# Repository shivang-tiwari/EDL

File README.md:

# EDL
This repository has all the work done in EDL, 2022

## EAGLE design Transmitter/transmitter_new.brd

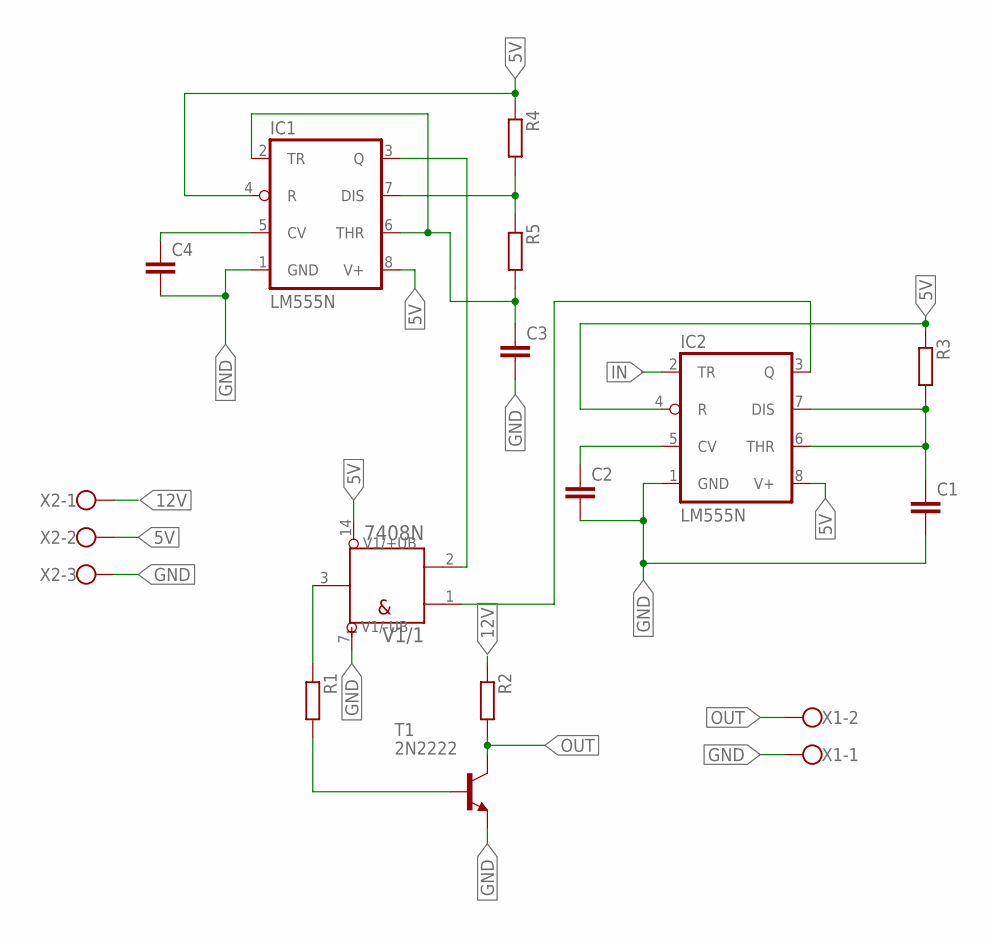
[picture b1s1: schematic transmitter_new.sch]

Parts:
C1, C2, C3, C4: C-EU050-025X075; C050-025X075
IC1, IC2: LM555N; DIL08
R1, R2, R3, R4, R5: R-EU_0207/10; 0207/10
T1: 2N2222; TO18
V1: 7408N; DIL14
X1: W237-102
X2: W237-103

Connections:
5V: IC1.4 (R), IC1.8 (V+), IC2.4 (R), IC2.8 (V+), R3.1, R4.1, V1.14 (+UB), X2.2
12V: R2.1, X2.1
GND: C1.2, C2.2, C3.2, C4.2, IC1.1 (GND), IC2.1 (GND), T1.1 (E), V1.7 (-UB), X1.1, X2.3
IN: IC2.2 (TR)
unnamed: IC1.7 (DIS), R4.2, R5.1
unnamed: C3.1, IC1.2 (TR), IC1.6 (THR), R5.2
unnamed: C4.1, IC1.5 (CV)
unnamed: IC1.3 (Q), V1.2 (B)
unnamed: C2.1, IC2.5 (CV)
unnamed: C1.1, IC2.6 (THR), IC2.7 (DIS), R3.2
unnamed: R1.1, V1.3 (Y)
unnamed: IC2.3 (Q), V1.1 (A)
unnamed: R1.2, T1.2 (B)
OUT: R2.2, T1.3 (C), X1.2

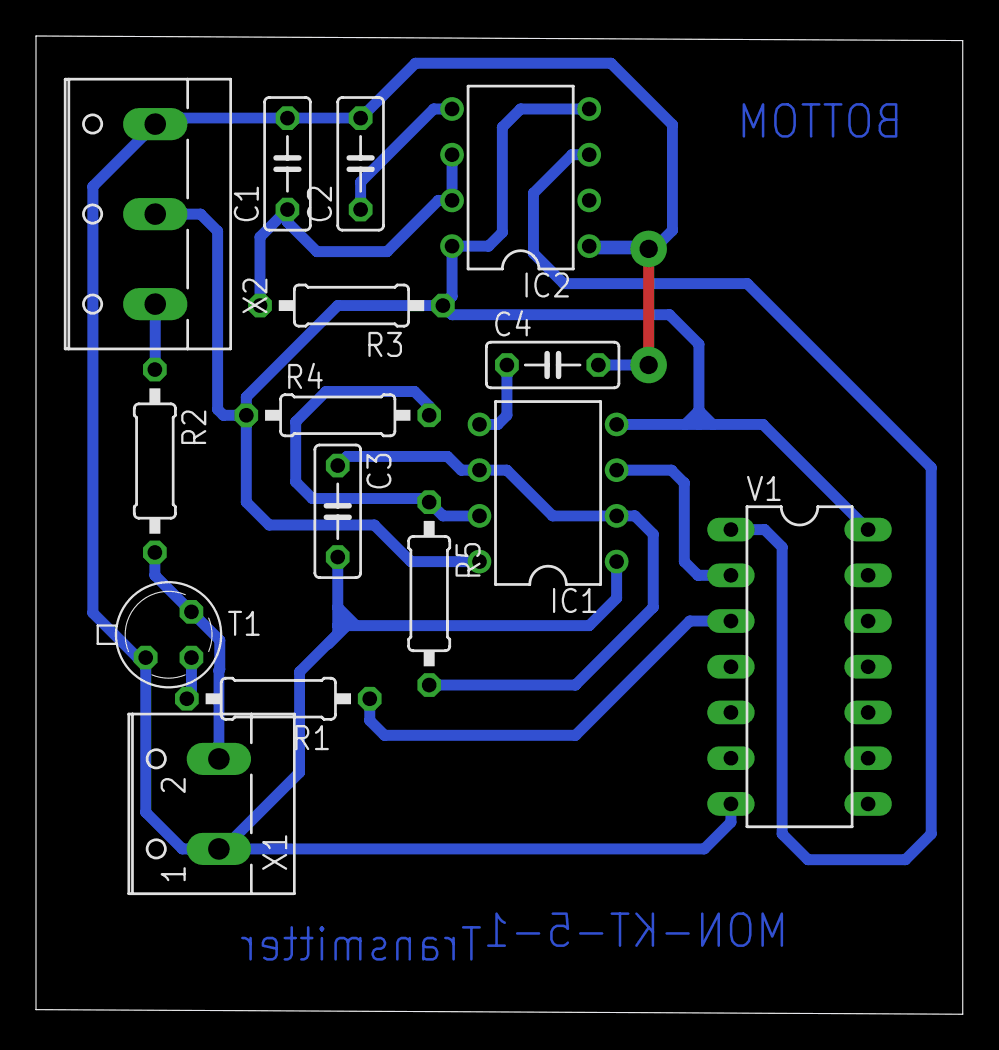
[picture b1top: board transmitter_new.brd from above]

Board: 2 copper layers, 51.5 x 54.3 mm, 15 parts (0 on the bottom side), 13 nets.

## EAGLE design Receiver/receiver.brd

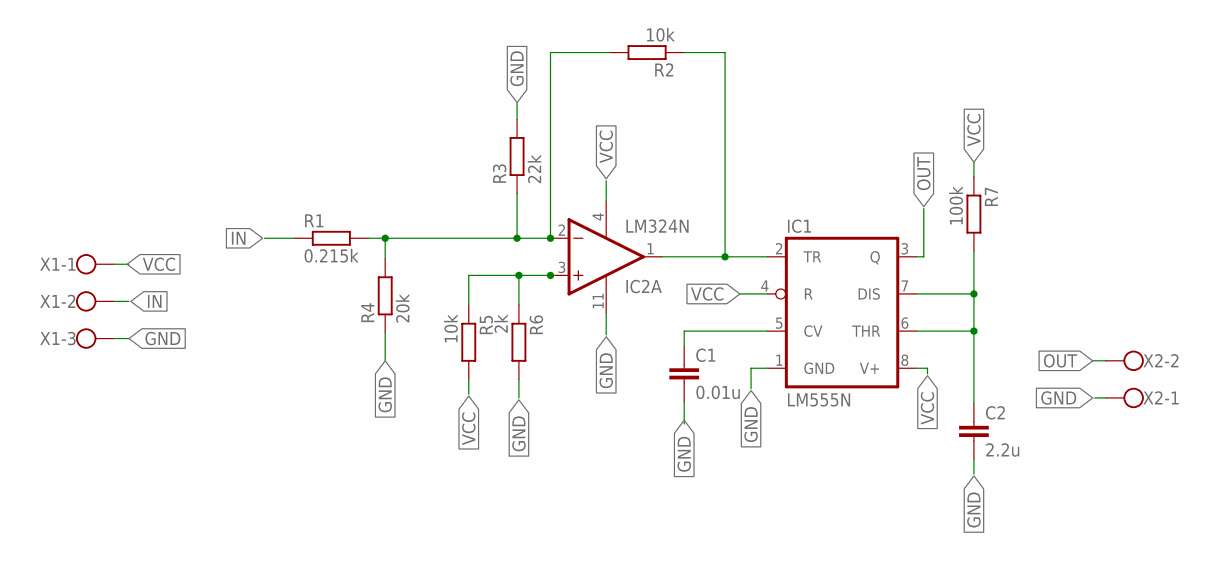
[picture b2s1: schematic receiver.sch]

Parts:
C1: 0.01u; C050-025X075
C2: 2.2u; C050-025X075
IC1: LM555N; DIL08
IC2: LM324N; DIL14
R1: 0.215k; 0207/10
R2, R5: 10k; 0207/10
R3: 22k; 0207/10
R4: 20k; 0207/10
R6: 2k; 0207/10
R7: 100k; 0207/10
X1: W237-103
X2: W237-102

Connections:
GND: C1.2, C2.2, IC1.1 (GND), IC2.11 (V-), R3.2, R4.1, R6.2, X1.3, X2.1
IN: R1.1, X1.2
unnamed: IC2.2 (-IN), R1.2, R2.2, R3.1, R4.2
unnamed: IC2.3 (+IN), R5.1, R6.1
unnamed: C2.1, IC1.6 (THR), IC1.7 (DIS), R7.2
unnamed: IC1.2 (TR), IC2.1 (OUT), R2.1
unnamed: C1.1, IC1.5 (CV)
OUT: IC1.3 (Q), X2.2
VCC: IC1.4 (R), IC1.8 (V+), IC2.4 (V+), R5.2, R7.1, X1.1

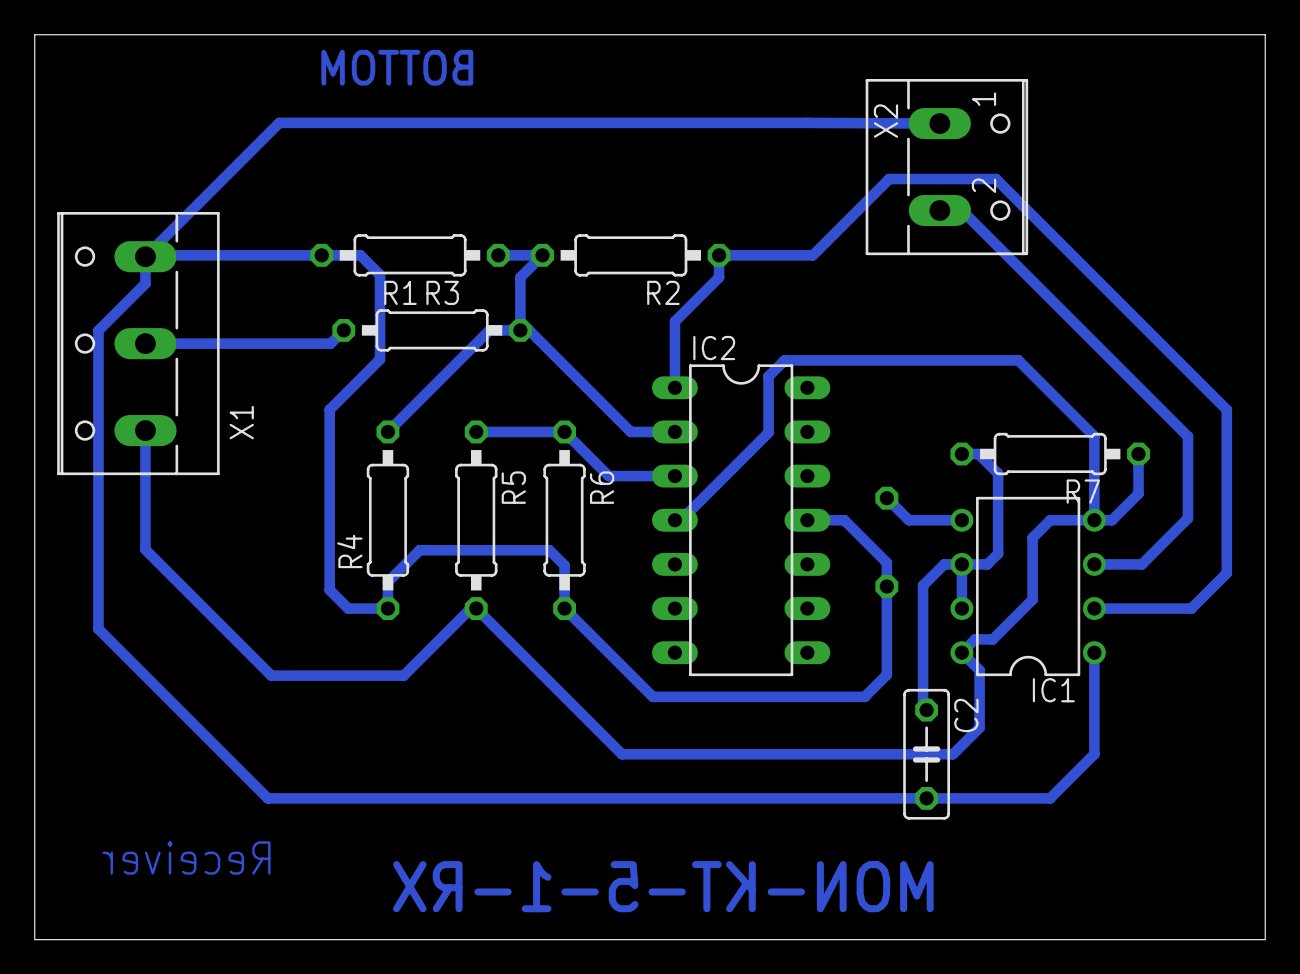
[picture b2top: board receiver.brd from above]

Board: 2 copper layers, 70.8 x 52.1 mm, 13 parts (1 on the bottom side), 9 nets.
